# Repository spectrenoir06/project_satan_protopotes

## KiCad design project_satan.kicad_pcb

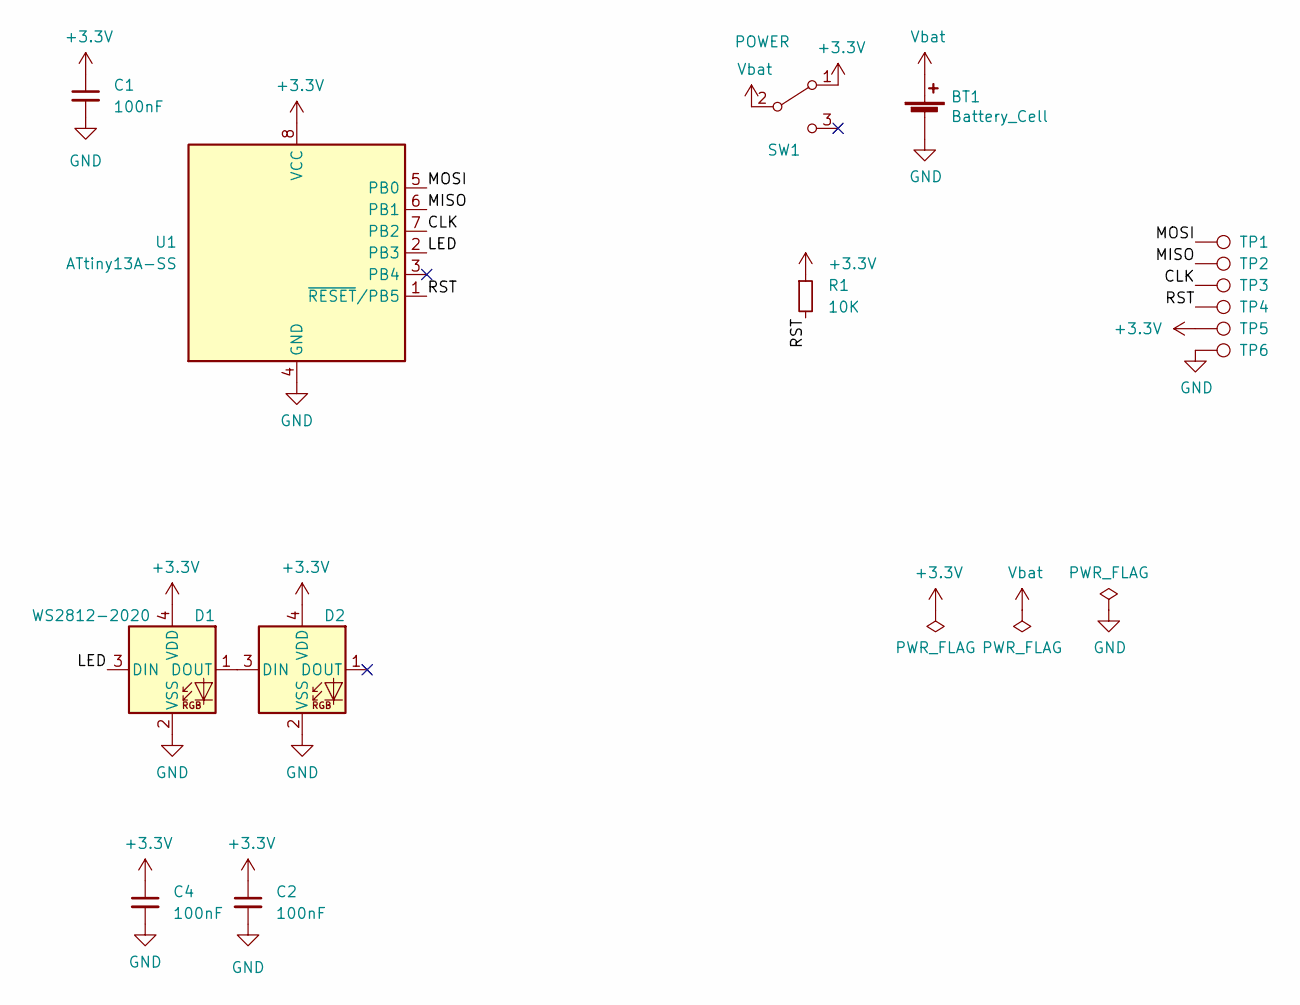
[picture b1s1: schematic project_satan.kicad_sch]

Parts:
BT1: Battery_Cell; BatteryHolder_Keystone_1058_1x2032; LCSC C70377
C1, C2, C4: 100nF; C_0603_1608Metric
D1, D2: WS2812-2020; ws2812-2020_reverse
R1: 10K; R_0603_1608Metric
SW1: POWER; SW_SPDT_PCM12; LCSC C319019
TP1, TP2, TP3, TP4, TP5, TP6: TestPoint; TestPoint_Pad_D1.0mm
U1: ATtiny13A-SS; SOIC-8_3.9x4.9mm_P1.27mm

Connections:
+3V3: C1.1, C2.1, C4.1, D1.4 (VDD), D2.4 (VDD), R1.1, SW1.1 (A), TP5.1, U1.8 (VCC)
/CLK: TP3.1, U1.7 (PB2)
/LED: D1.3 (DIN), U1.2 (PB3)
/MISO: TP2.1, U1.6 (PB1)
/MOSI: TP1.1, U1.5 (PB0)
/RST: R1.2, TP4.1, U1.1 (~RESET/PB5)
GND: BT1.2 (-), C1.2, C2.2, C4.2, D1.2 (VSS), D2.2 (VSS), TP6.1, U1.4 (GND)
unnamed: D1.1 (DOUT), D2.3 (DIN)
VBAT: BT1.1 (+), SW1.2 (B)

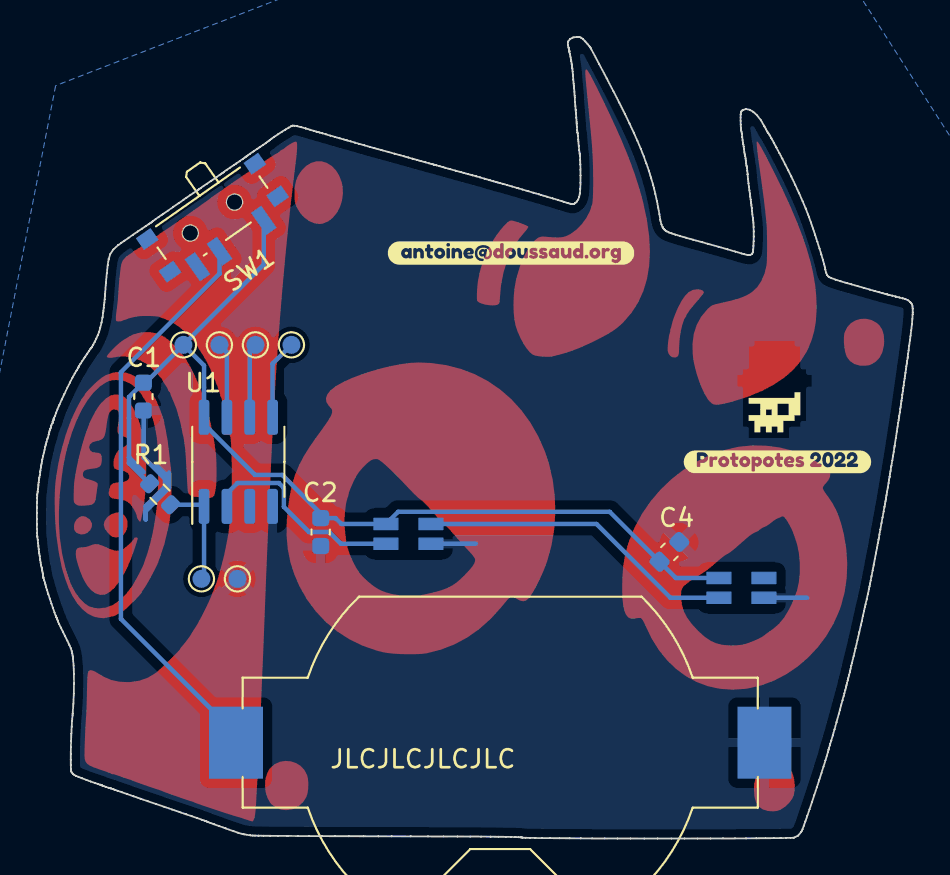
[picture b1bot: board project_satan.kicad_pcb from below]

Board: 2 copper layers, 48.7 x 44.5 mm, 17 parts (17 on the bottom side), 9 nets.

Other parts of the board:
kibuzzard-63449642: G***; kibuzzard-63449642
kibuzzard-63472777: G***; kibuzzard-63472777

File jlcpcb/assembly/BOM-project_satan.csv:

Comment,Designator,Footprint,LCSC
POWER,SW1,SW_SPDT_PCM12,C319019
Battery_Cell,BT1,BatteryHolder_Keystone_1058_1x2032,C70377
10K,R1,R_0603_1608Metric,
ATtiny13A-SS,U1,SOIC-8_3.9x4.9mm_P1.27mm,
TestPoint,TP6,TestPoint_Pad_D1.0mm,
TestPoint,TP5,TestPoint_Pad_D1.0mm,
TestPoint,TP4,TestPoint_Pad_D1.0mm,
TestPoint,TP3,TestPoint_Pad_D1.0mm,
TestPoint,TP2,TestPoint_Pad_D1.0mm,
TestPoint,TP1,TestPoint_Pad_D1.0mm,
100nF,C4,C_0603_1608Metric,
10uF,C1,C_0603_1608Metric,
WS2812-2020,D2,ws2812-2020_reverse,
WS2812-2020,D1,ws2812-2020_reverse,
100nF,C2,C_0603_1608Metric,

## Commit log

2022-11-06 init
